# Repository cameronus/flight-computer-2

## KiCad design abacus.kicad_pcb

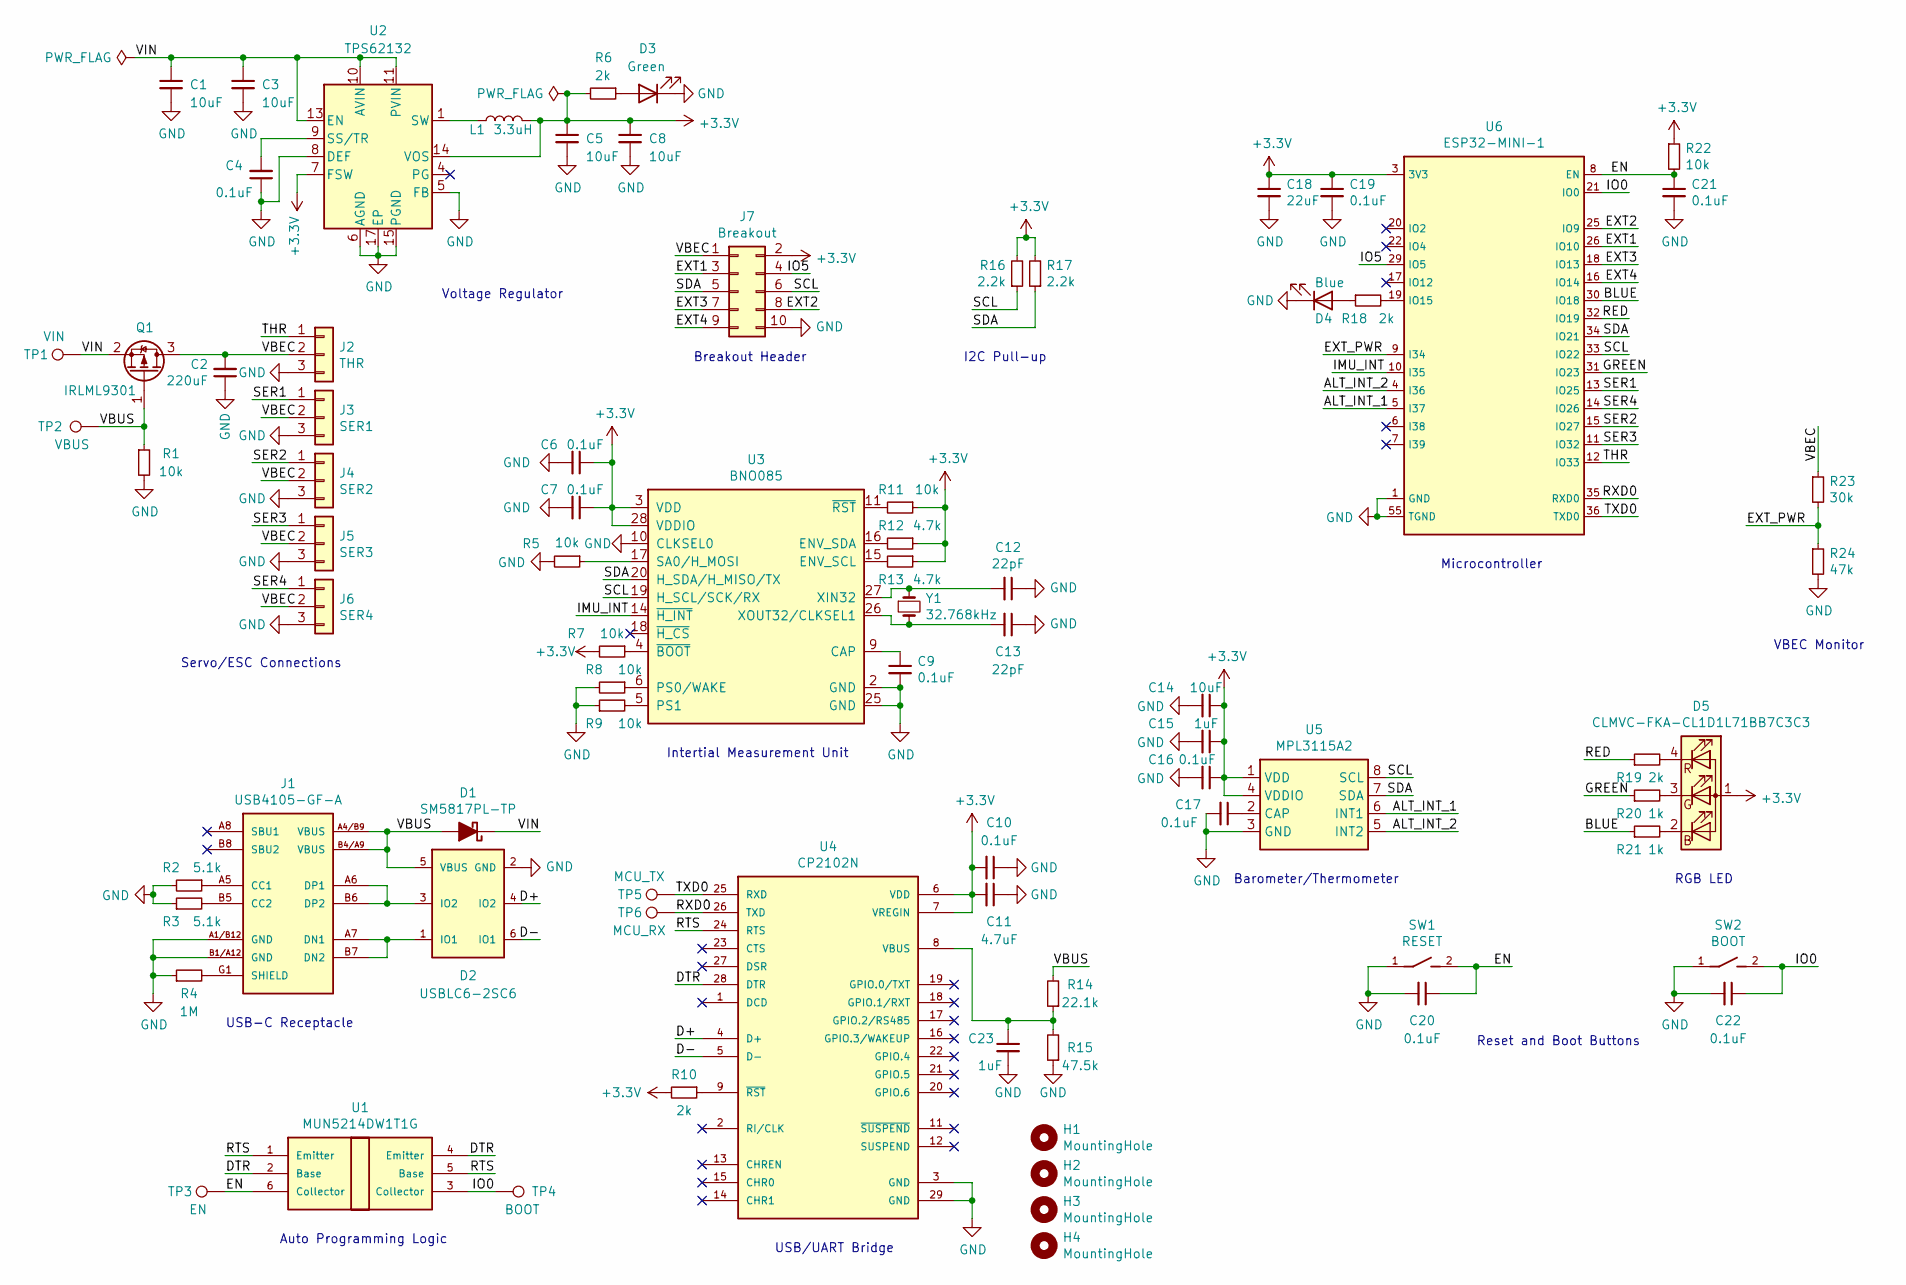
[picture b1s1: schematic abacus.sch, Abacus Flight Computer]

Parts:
C1, C3, C5, C8, C14: 10uF; C_0805_2012Metric; MPN CL21B106KOQNNNE
C2: 220uF; C_1206_3216Metric; MPN GRM31CR60J227ME11L
C4, C6, C7, C9, C10, C16, C17, C19, C20, C21, C22: 0.1uF; C_0603_1608Metric; MPN CL10B104KB8NNNC
C11: 4.7uF; C_0603_1608Metric; MPN CL10B475KQ8NQNC
C12, C13: 22pF; C_0603_1608Metric; MPN C0603C220K4GACTU
C15, C23: 1uF; C_0603_1608Metric; MPN CL10B105KP8NNNC
C18: 22uF; C_1206_3216Metric; MPN CL31B226KPHNNNE
D1: SM5817PL-TP; D_SOD-123F; MPN SM5817PL-TP
D2: USBLC6-2SC6; SOT-23-6; MPN USBLC6-2SC6
D3: Green; LED_0603_1608Metric; MPN LTST-C191KGKT
D4: Blue; LED_0603_1608Metric; MPN LTST-C191TBKT
D5: CLMVC-FKA-CL1D1L71BB7C3C3; LED_Cree-PLCC4_2x2mm_CW; MPN CLMVC-FKA-CL1D1L71BB7C3C3
H1, H2, H3, H4: MountingHole; MountingHole_2.2mm_M2_Pad
J1: USB4105-GF-A; GCT_USB4105-GF-A; MPN USB4105-GF-A
J2: THR; PinHeader_1x03_P2.54mm_Vertical
J3: SER1; PinHeader_1x03_P2.54mm_Vertical
J4: SER2; PinHeader_1x03_P2.54mm_Vertical
J5: SER3; PinHeader_1x03_P2.54mm_Vertical
J6: SER4; PinHeader_1x03_P2.54mm_Vertical
J7: Breakout; PinHeader_2x05_P2.54mm_Vertical
L1: 3.3uH; 0420CDMCCDS; MPN 0420CDMCCDS-3R3MC
Q1: IRLML9301; SOT-23; MPN IRLML9301
R1, R5, R7, R8, R9, R11, R22: 10k; R_0603_1608Metric; MPN RC0603FR-0710KL
R2, R3: 5.1k; R_0603_1608Metric; MPN RC0603FR-075K1L
R4: 1M; R_0603_1608Metric; MPN RC0603FR-071ML
R6, R10, R18, R19: 2k; R_0603_1608Metric; MPN RC0603FR-072KL
R12, R13: 4.7k; R_0603_1608Metric; MPN RC0603FR-074K7L
R14: 22.1k; R_0603_1608Metric; MPN RC0603FR-0722K1L
R15: 47.5k; R_0603_1608Metric; MPN RC0603FR-0747K5L
R16, R17: 2.2k; R_0603_1608Metric; MPN RC0603FR-072K2L
R20, R21: 1k; R_0603_1608Metric; MPN RC0603FR-071KL
R23: 30k; R_0603_1608Metric; MPN RC0603FR-0730KL
R24: 47k; R_0603_1608Metric; MPN RC0603FR-0747KL
SW1: RESET; SW_SPST_PTS810; MPN PTS810 SJK 250 SMTR LFS
SW2: BOOT; SW_SPST_PTS810; MPN PTS810 SJK 250 SMTR LFS
TP1: VIN; TestPoint_Pad_D1.5mm
TP2: VBUS; TestPoint_Pad_D1.5mm
TP3: EN; TestPoint_Pad_D1.5mm
TP4: BOOT; TestPoint_Pad_D1.5mm
TP5: MCU_TX; TestPoint_Pad_D1.5mm
TP6: MCU_RX; TestPoint_Pad_D1.5mm
U1: MUN5214DW1T1G; SOT-363_SC-70-6; MPN MUN5214DW1T1G
U2: TPS62132; VQFN-16-1EP_3x3mm_P0.5mm_EP1.68x1.68mm_ThermalVias; MPN TPS62132RGTR
U3: BNO085; LGA-28_5.2x3.8mm_P0.5mm; MPN BNO085
U4: CP2102N; QFN-28-1EP_5x5mm_P0.5mm_EP3.35x3.35mm; MPN CP2102N-A02-GQFN28R
U5: MPL3115A2; LGA-8_3x5mm_P1.25mm; MPN MPL3115A2R1
U6: ESP32-MINI-1; MPN ESP32-MINI-1
Y1: 32.768kHz; ABS07; MPN ABS07-32.768KHZ-1-T

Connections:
+3V3: C5.1, C6.1, C7.1, C8.1, C10.2, C11.2, C14.1, C15.1, C16.1, C18.1, C19.1, D5.1 (A), J7.2, L1.2, R6.2, R7.2, R10.2, R11.1, R12.1, R13.1, R16.2, R17.2, R22.1, U2.7 (FSW), U2.14 (VOS), U3.3 (VDD), U3.28 (VDDIO), U4.6 (VDD), U4.7 (VREGIN), U5.1 (VDD), U5.4 (VDDIO), U6.3 (3V3)
/ALT_INT_1: U5.6 (INT1), U6.5 (I37)
/ALT_INT_2: U5.5 (INT2), U6.4 (I36)
/BLUE: R21.1, U6.30 (IO18)
/D+: D2.4 (IO2), U4.4 (D+)
/D-: D2.6 (IO1), U4.5 (D-)
/DTR: U1.2 (Base), U1.4 (Emitter), U4.28 (DTR)
/EN: C20.1, C21.1, R22.2, SW1.2, TP3.1, U1.6 (Collector), U6.8 (EN)
/EXT1: J7.3, U6.26 (IO10)
/EXT2: J7.8, U6.25 (IO9)
/EXT3: J7.7, U6.18 (IO13)
/EXT4: J7.9, U6.16 (IO14)
/EXT_PWR: R23.2, R24.1, U6.9 (I34)
/GREEN: R20.1, U6.31 (IO23)
/IMU_INT: U3.14 (~H_INT), U6.10 (I35)
/IO0: C22.1, SW2.2, TP4.1, U1.3 (Collector), U6.21 (IO0)
/IO5: J7.4, U6.29 (IO5)
/RED: R19.1, U6.32 (IO19)
/RTS: U1.1 (Emitter), U1.5 (Base), U4.24 (RTS)
/RXD0: TP6.1, U4.26 (TXD), U6.35 (RXD0); also elsewhere on the board
/SCL: J7.6, R16.1, U3.19 (H_SCL/SCK/RX), U5.8 (SCL), U6.33 (IO22)
/SDA: J7.5, R17.1, U3.20 (H_SDA/H_MISO/TX), U5.7 (SDA), U6.34 (IO21)
/SER1: J3.1, U6.13 (IO25)
/SER2: J4.1, U6.15 (IO27)
/SER3: J5.1, U6.11 (IO32)
/SER4: J6.1, U6.14 (IO26)
/THR: J2.1, U6.12 (IO33)
/TXD0: TP5.1, U4.25 (RXD), U6.36 (TXD0); also elsewhere on the board
/VBEC: C2.2, J2.2, J3.2, J4.2, J5.2, J6.2, J7.1, Q1.3 (D), R23.1
/VBUS: D1.2 (A), D2.5 (VBUS), J1.A4/B9 (VBUS), J1.B4/A9 (VBUS), Q1.1 (G), R1.1, R14.2, TP2.1; also elsewhere on the board
/VIN: C1.1, C3.1, D1.1 (K), Q1.2 (S), TP1.1, U2.10 (AVIN), U2.11 (PVIN), U2.12 (PVIN), U2.13 (EN); also elsewhere on the board
GND: C1.2, C2.1, C3.2, C4.1, C5.2, C6.2, C7.2, C8.2, C9.2, C10.1, C11.1, C12.1, C13.1, C14.2, C15.2, C16.2, C17.2, C18.2, C19.2, C20.2, C21.2, C22.2, C23.2, D2.2 (GND), D3.1 (K), D4.1 (K), J1.A1/B12 (GND), J1.B1/A12 (GND), J2.3, J3.3, J4.3, J5.3, J6.3, J7.10, R1.2, R2.2, R3.1, R4.1, R5.2, R8.2, R9.1, R15.1, R24.2, SW1.1, SW2.1, U2.5 (FB), U2.6 (AGND), U2.8 (DEF), U2.15 (PGND), U2.16 (PGND), U2.17 (EP), U3.2 (GND), U3.10 (CLKSEL0), U3.25 (GND), U4.3 (GND), U4.29 (GND), U5.3 (GND), U6.1 (GND), U6.2 (GND), U6.27 (GND), U6.38 (GND), U6.39 (GND), U6.40 (GND), U6.41 (GND), U6.42 (GND), U6.43 (GND), U6.44 (GND), U6.45 (GND), U6.46 (GND), U6.47 (GND), U6.48 (GND), U6.49 (GND), U6.50 (GND), U6.51 (GND), U6.52 (GND), U6.53 (GND), U6.54 (GND), U6.55 (TGND)
unnamed: C4.2, U2.9 (SS/TR)
unnamed: C9.1, U3.9 (CAP)
unnamed: C12.2, U3.27 (XIN32), Y1.1
unnamed: C13.2, U3.26 (XOUT32/CLKSEL1), Y1.2
unnamed: C17.1, U5.2 (CAP)
unnamed: C23.1, R14.1, R15.2, U4.8 (VBUS)
unnamed: D2.1 (IO1), J1.A7 (DN1), J1.B7 (DN2)
unnamed: D2.3 (IO2), J1.A6 (DP1), J1.B6 (DP2)
unnamed: D3.2 (A), R6.1
unnamed: D4.2 (A), R18.1
unnamed: D5.2 (B), R21.2
unnamed: D5.3 (G), R20.2
unnamed: D5.4 (R), R19.2
unnamed: J1.A5 (CC1), R2.1
unnamed: J1.B5 (CC2), R3.2
unnamed: J1.G1 (SHIELD), J1.G2 (SHIELD), J1.G3 (SHIELD), J1.G4 (SHIELD), R4.2
unnamed: L1.1, U2.1 (SW), U2.2 (SW), U2.3 (SW)
unnamed: R5.1, U3.17 (SA0/H_MOSI)
unnamed: R7.1, U3.4 (~BOOT)
unnamed: R8.1, U3.6 (PS0/WAKE)
unnamed: R9.2, U3.5 (PS1)
unnamed: R10.1, U4.9 (~RST~)
unnamed: R11.2, U3.11 (~RST)
unnamed: R12.2, U3.16 (ENV_SDA)
unnamed: R13.2, U3.15 (ENV_SCL)
unnamed: R18.2, U6.19 (IO15)

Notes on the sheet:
Voltage Regulator
Servo/ESC Connections
USB-C Receptacle
Intertial Measurement Unit
USB/UART Bridge
Auto Programming Logic
Barometer/Thermometer
Reset and Boot Buttons
I2C Pull-up
RGB LED
Breakout Header
VBEC Monitor
Microcontroller

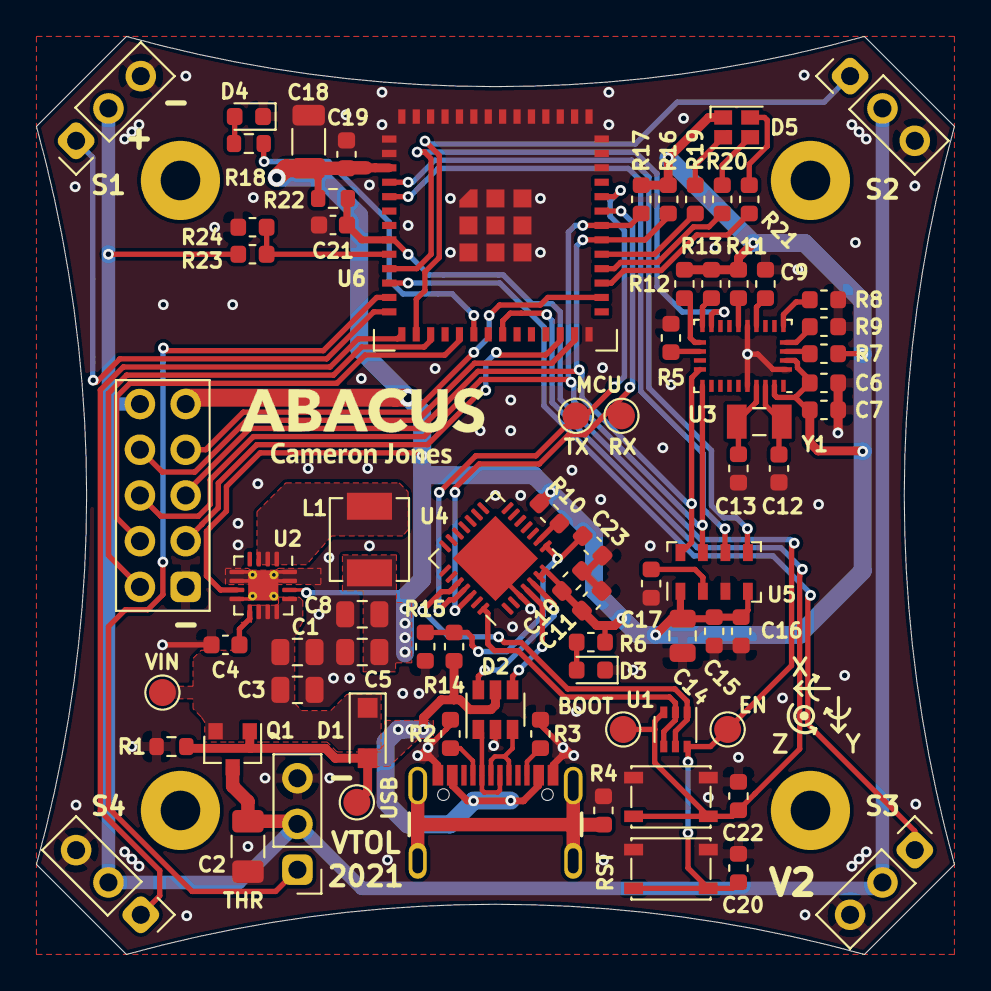
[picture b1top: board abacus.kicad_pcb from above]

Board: 2 copper layers, 51.0 x 51.0 mm, 80 parts (0 on the bottom side), 58 nets.

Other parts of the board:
RX: MCU_RX; TestPoint_Pad_D1.5mm
TX: MCU_TX; TestPoint_Pad_D1.5mm
USB: VBUS; TestPoint_Pad_D1.5mm
VIN: VIN; TestPoint_Pad_D1.5mm

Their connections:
/RXD0: RX.1; also elsewhere on the board
/TXD0: TX.1; also elsewhere on the board
/VBUS: USB.1; also elsewhere on the board
/VIN: VIN.1; also elsewhere on the board

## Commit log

2020-07-16 New USB symbol
2020-07-16 Finishing MCU portion of schematic
2020-07-16 Fixed ERC issues
2020-07-18 IMU and barometer circuitry
2020-07-18 Servo capacitors
2020-07-18 Fixed ERC errors
2020-07-18 Labels and USB/UART bridge correction
2020-07-19 Switched diode and added current limiting resistors
2020-07-19 New microSD card symbol
2020-07-20 Added RGB LED
2020-07-21 I2C lines and new servo power filtering caps
2020-07-21 Associating MPNs with symbols
2020-07-24 Pin assignments
2020-07-24 Breakout headers
2020-07-25 Created footprint library
2020-07-25 Connecting interrupt pins
2020-07-25 Assigning footprints
2020-07-29 New USB ESD protection IC
2020-07-29 New antenna
2020-07-30 New voltage regulator and diode
2020-07-30 MOSFET to detect external power
2020-07-30 Voltage divider and updated servo inrush resistors
2020-07-30 Rough PCB layout
2020-07-30 Mounting holes and more component placement
2020-07-30 Adjusting 3D model offset and more placement
2020-07-30 More placement and footprint updates
2020-07-30 Finished preliminary placement
2020-07-31 More layout and routing
2020-07-31 USB/UART routing complete
2020-07-31 MCU and sensor routing
2020-07-31 Restarting routing with smaller passive footprints
2020-07-31 New 3D models and testing placement
2020-08-01 Further arrangement and new MCU footprint
2020-08-01 More optimization
2020-08-01 Upscaled to 0603 passives
2020-08-01 USB/Vreg routing
2020-08-01 MCU routing partially complete
2020-08-01 Fixed footprint of ESP32
2020-08-01 Centered ICs and rerouted traces
2020-08-01 3D model for crystal
2020-08-02 I2C and other crucial signals routed
2020-08-02 Refactoring pin mapping
2020-08-02 Rerouting progress
2020-08-02 Final draft of routing complete
2020-08-03 Small adjustments and IC silkscreen
2020-08-03 VBEC power filtering cap
2020-08-03 Fixed reference silkscreen
2020-08-04 Finished top silkscreen and enabled bottom layers
2020-08-04 Fix strapping pin being pulled high to prevent boot failure
2020-08-04 Better solution to strapping pin issue
2020-08-04 Small routing changes
2020-08-04 New power filtering cap and minor routing adjustments
2020-08-04 Removing programming selector resistors
2020-08-04 More vias near antenna pads
2020-08-05 Added MPNs for passives and modified SW symbols
2020-08-05 Readded 3D model for buttons
2020-08-05 More silkscreen fixes and switched MPN
2020-08-05 Small routing change
2020-08-05 Gerbers, BOM, and centroid file
2020-08-07 IMU axis marker and small routing changes
2020-08-07 New graphics/gerbers/centroid file
2020-08-07 Production revision
2020-08-09 Servo labels and microstrip grounding vias
2020-08-29 Small routing/silk changes
2021-01-17 Switching to ESP32-MINI-1 module
2021-01-18 Status LED and breakout pins
2021-01-18 BNO upgrade and address selection
2021-01-20 DCDC regulator and reverse current MOSFET
2021-01-21 Updated annotations and parts
2021-01-21 Update switch actuation force
2021-01-21 New parts, annotation
2021-01-22 Fix footprint association
2021-01-22 Updated PCB with new netlist/footprints
2021-01-23 Layout and fixing passive footprint
2021-01-24 Layout and routing
2021-01-25 Routing draft
2021-01-25 Cleaning up routing
2021-01-25 More refinement
2021-01-25 Finalizing routing
2021-01-25 Improved grounding
2021-01-25 Grounding and layout refinement
2021-01-25 Inductor 3D model
2021-01-25 Opened thermal vias and fixed routing bug
2021-01-25 Silkscreen
2021-01-25 Switching regulator 3D model
2021-01-25 Silkscreen labels
2021-01-26 Final touches and gerbers
2021-01-26 More labels
2021-01-26 Updated BOM
2021-01-28 Interactive BOM
2021-02-07 Renaming project
